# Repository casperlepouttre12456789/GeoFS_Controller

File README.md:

BOM

The materials required are:
2 joysticks (drone controller or playstation type)
2 220 ohm resistors
5 MX-style switches
2 4 mm LEDs (can be any color but I used red and green)
seeeduino rp 2040
3D-printed case and
custom pcb 

Assembly

PCB assembly is pretty straightforward if there is a white line between 2 holes; you need to connect them on the back, and then you just put it in the case and put the top one on (it should stay on without screws), and I will also make a tutorial when I get the PCB.

Setting up

Setting up is pretty simple; you just flash the main.py to your Xiao RP2040, and then you are going to have to launch Geofs and use the trim button to get the cursor in the middle (first time only, this saves).
Then you are going to want to bind keys to actions. What I did was 1, trim, but you can’t change the keybind for this one without messing with the code; 2 is landing gear toggle automatically but you can change buttons 2 to 5 in keybinds; 3, flaps toggle; 4, airbrake; and 5, wheel brake (has to stay wheelbrake because this one isn’t a toggle)

Using the hackpad

Just launch Geofs and plug it in and enjoy :)

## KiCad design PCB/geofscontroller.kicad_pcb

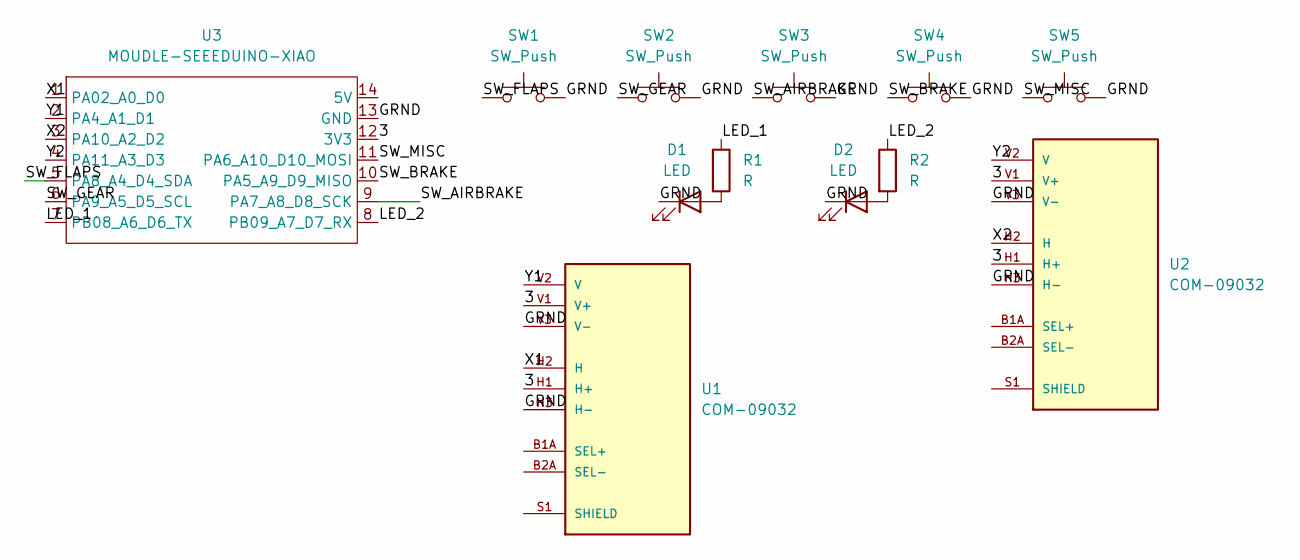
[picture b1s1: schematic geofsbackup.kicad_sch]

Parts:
D1, D2: LED
R1, R2: R
SW1, SW2, SW3, SW4, SW5: SW_Push
U1, U2: COM-09032; XDCR_COM-09032; PARTREV N/A
U3: MOUDLE-SEEEDUINO-XIAO

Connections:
/3: U1.H1 (H+), U1.V1 (V+), U2.H1 (H+), U2.V1 (V+), U3.12 (3V3)
/GRND: D1.1 (K), D2.1 (K), SW1.2, SW2.2, SW3.2, SW4.2, SW5.2, U1.H3 (H-), U1.V3 (V-), U2.H3 (H-), U2.V3 (V-), U3.13 (GND)
/LED_1: R1.1, U3.7 (PB08_A6_D6_TX)
/LED_2: R2.1, U3.8 (PB09_A7_D7_RX)
/SW_AIRBRAKE: SW3.1, U3.9 (PA7_A8_D8_SCK)
/SW_BRAKE: SW4.1, U3.10 (PA5_A9_D9_MISO)
/SW_FLAPS: SW1.1, U3.5 (PA8_A4_D4_SDA)
/SW_GEAR: SW2.1, U3.6 (PA9_A5_D5_SCL)
/SW_MISC: SW5.1, U3.11 (PA6_A10_D10_MOSI)
/X1: U1.H2 (H), U3.1 (PA02_A0_D0)
/X2: U2.H2 (H), U3.3 (PA10_A2_D2)
/Y1: U1.V2 (V), U3.2 (PA4_A1_D1)
/Y2: U2.V2 (V), U3.4 (PA11_A3_D3)
unnamed: D1.2 (A), R1.2
unnamed: D2.2 (A), R2.2
unnamed: U1.S1 (SHIELD), U1.S2 (SHIELD), U1.S3 (SHIELD), U1.S4 (SHIELD)
unnamed: U2.S1 (SHIELD), U2.S2 (SHIELD), U2.S3 (SHIELD), U2.S4 (SHIELD)

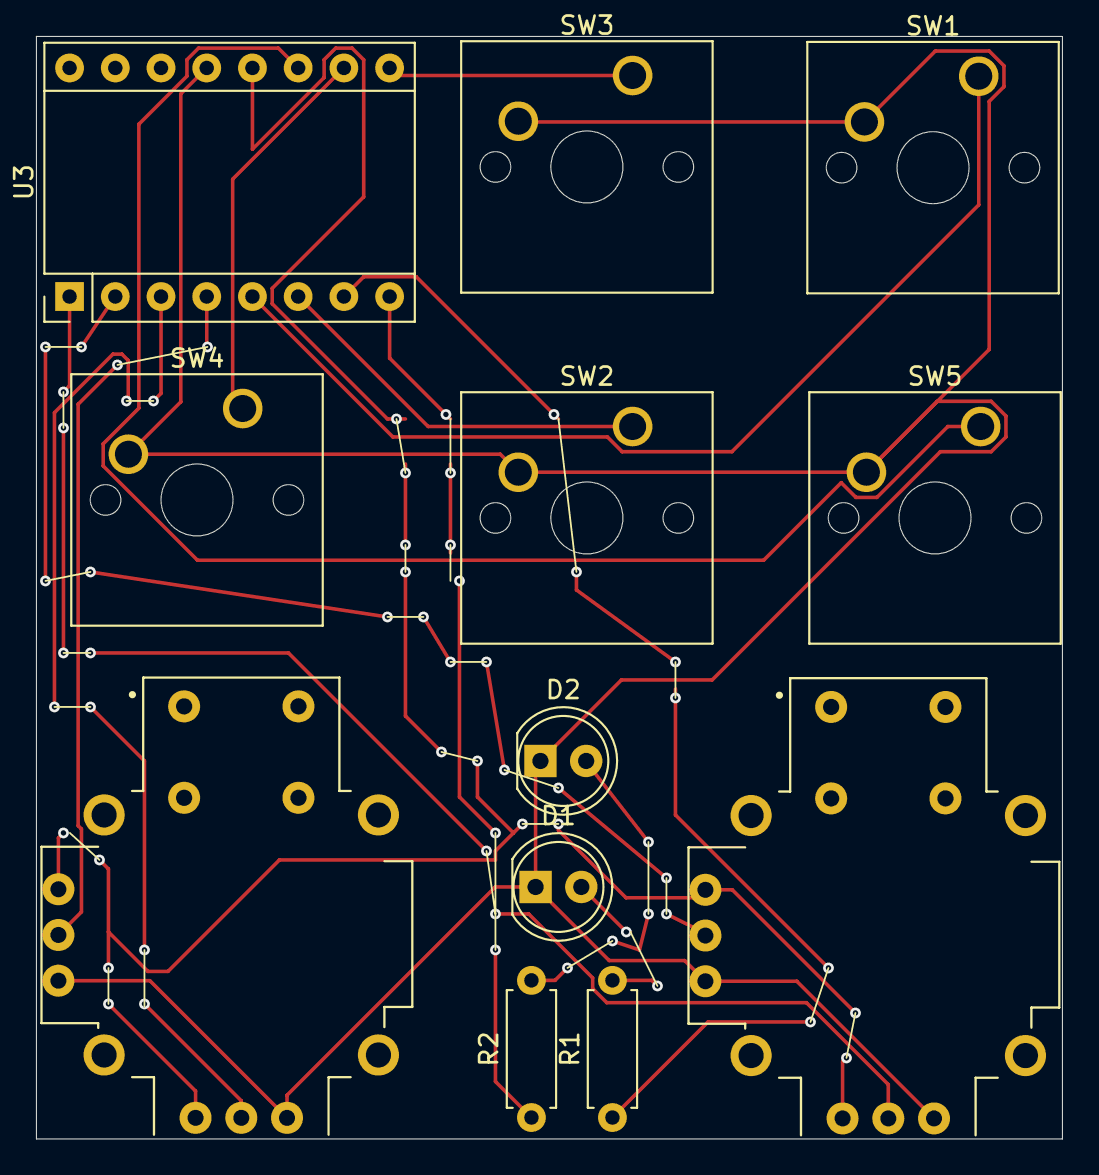
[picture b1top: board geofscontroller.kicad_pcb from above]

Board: 2 copper layers, 57.0 x 61.2 mm, 12 parts (0 on the bottom side), 17 nets.

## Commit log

2026-06-18 Finalized GeoFS control logic with mouse emulation
2026-06-18 cleanup
